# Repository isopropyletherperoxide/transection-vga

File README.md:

# transection-vga 

A breakout board for putting yourself in the middle of a VGA signal chain. Intended (mostly) for experimentation and glitch art.

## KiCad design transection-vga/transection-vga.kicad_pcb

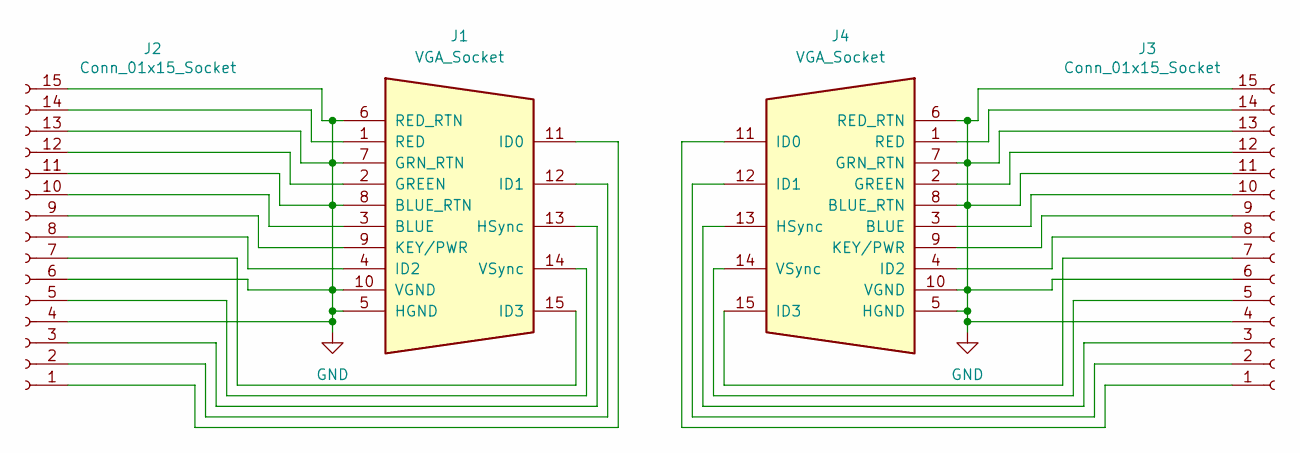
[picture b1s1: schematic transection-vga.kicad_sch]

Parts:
J1, J4: VGA_Socket; DSUB-15-HD_Socket_Horizontal_P2.29x2.54mm_EdgePinOffset8.35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
J2, J3: Conn_01x15_Socket; PinSocket_1x15_P2.54mm_Vertical

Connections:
GND: J1.5 (HGND), J1.6 (RED_RTN), J1.7 (GRN_RTN), J1.8 (BLUE_RTN), J1.10 (VGND), J2.4, J2.6, J2.11, J2.13, J2.15, J3.4, J3.6, J3.11, J3.13, J3.15, J4.5 (HGND), J4.6 (RED_RTN), J4.7 (GRN_RTN), J4.8 (BLUE_RTN), J4.10 (VGND)
unnamed: J1.3 (BLUE), J2.10
unnamed: J1.2 (GREEN), J2.12
unnamed: J1.13 (HSync), J2.3
unnamed: J1.11 (ID0), J2.1
unnamed: J1.12 (ID1), J2.2
unnamed: J1.4 (ID2), J2.8
unnamed: J1.15 (ID3), J2.7
unnamed: J1.9 (KEY/PWR), J2.9
unnamed: J1.1 (RED), J2.14
unnamed: J1.14 (VSync), J2.5
unnamed: J3.1, J4.11 (ID0)
unnamed: J3.2, J4.12 (ID1)
unnamed: J3.3, J4.13 (HSync)
unnamed: J3.5, J4.14 (VSync)
unnamed: J3.7, J4.15 (ID3)
unnamed: J3.8, J4.4 (ID2)
unnamed: J3.9, J4.9 (KEY/PWR)
unnamed: J3.10, J4.3 (BLUE)
unnamed: J3.12, J4.2 (GREEN)
unnamed: J3.14, J4.1 (RED)

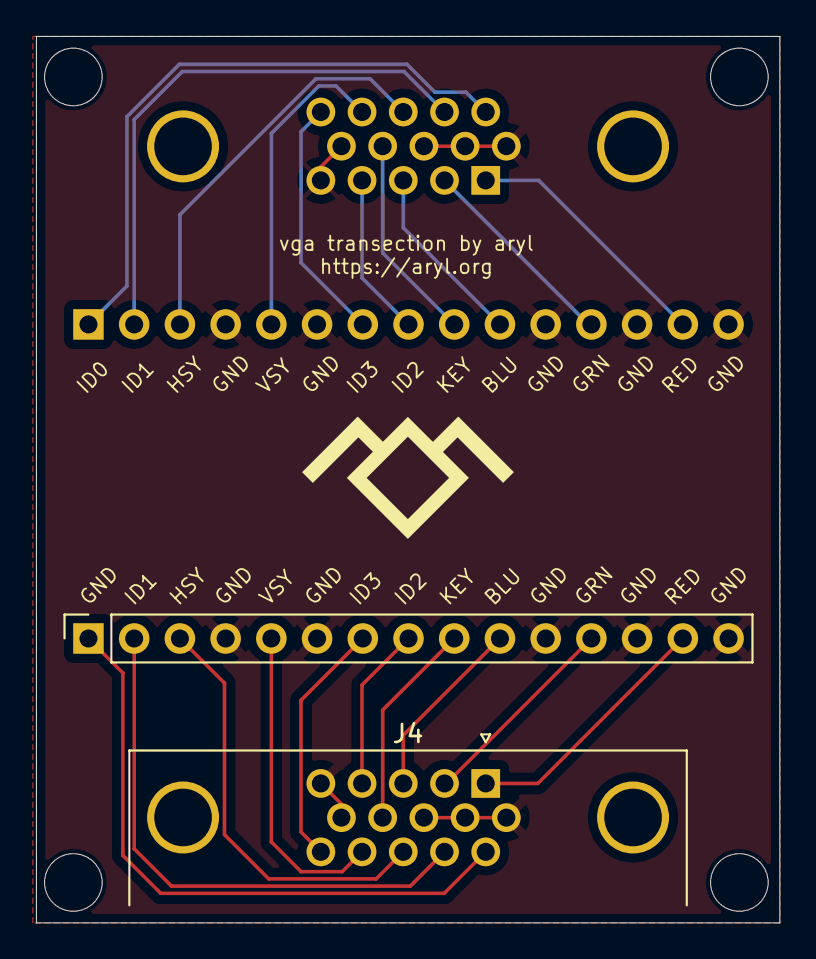
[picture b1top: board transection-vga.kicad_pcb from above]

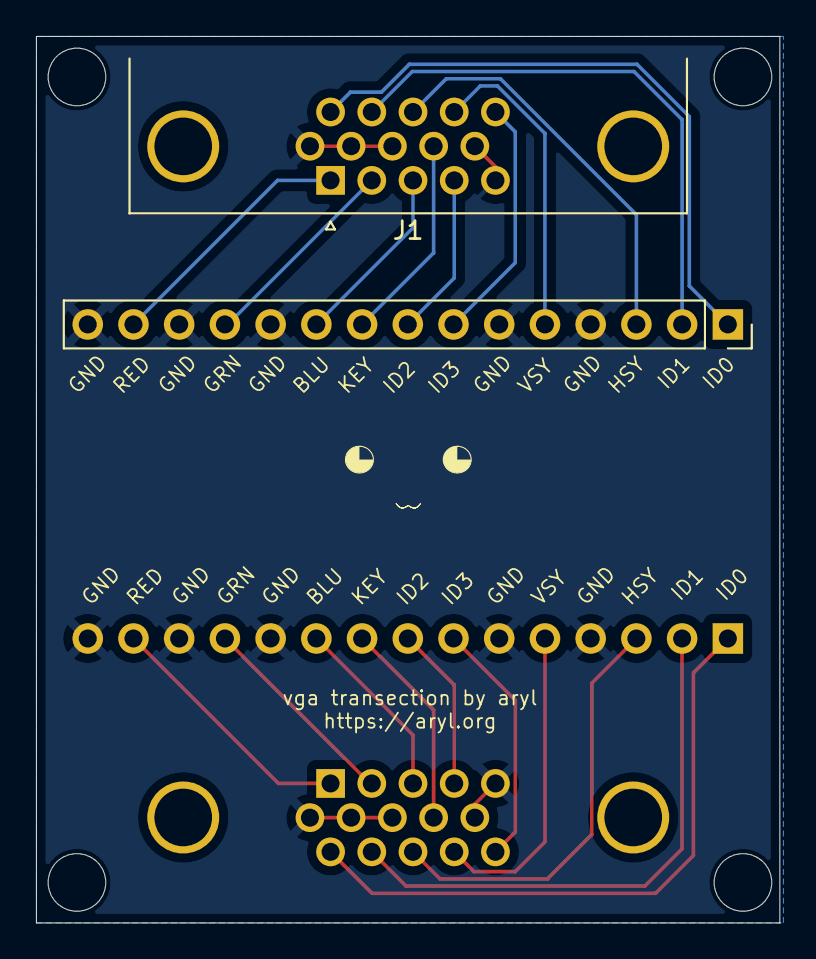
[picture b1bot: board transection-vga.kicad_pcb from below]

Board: 2 copper layers, 41.3 x 49.2 mm, 4 parts (2 on the bottom side), 21 nets.

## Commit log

2025-10-17 grbr cleanup
2025-10-17 image
2025-10-17 gerbers
2025-10-17 readme
2025-10-17 fluff
2025-10-18 pcb edits
